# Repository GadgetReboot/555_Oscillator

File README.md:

# 555_Oscillator
555 Oscillator with Duty Cycle and Frequency Control
<br><br><BR><BR>

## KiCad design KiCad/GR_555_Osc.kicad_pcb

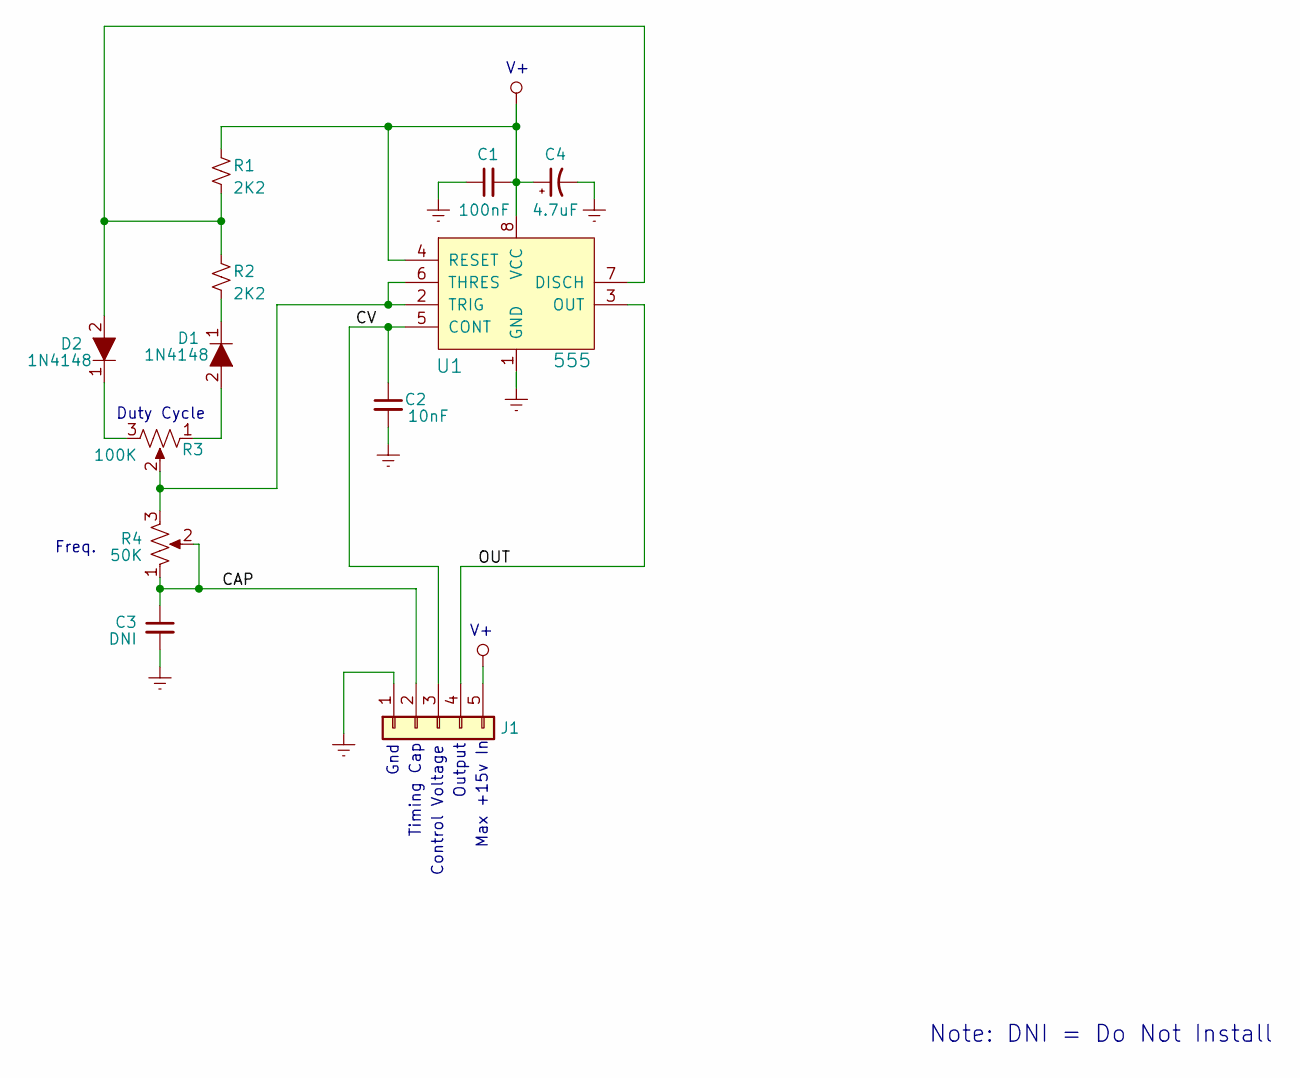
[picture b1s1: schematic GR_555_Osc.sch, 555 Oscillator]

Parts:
C1: 100nF; C_Disc_D3.8mm_W2.6mm_P2.50mm
C2: 10nF; C_Disc_D3.8mm_W2.6mm_P2.50mm
C3: DNI; C_Disc_D3.8mm_W2.6mm_P2.50mm
C4: 4.7uF; CP_Radial_D5.0mm_P2.50mm
D1, D2: 1N4148; Diode_DO-35_P10mm; MPN 1N4148; Digi-Key_PN 1N4148FS-ND
J1: Conn_01x05; PinHeader_1x05_P2.54mm_Vertical
R1, R2: 2K2; R_Axial_DIN0207_L6.3mm_D2.5mm_P10.16mm_Horizontal
R3: 100K; Potentiometer_Bourns_PTV09A-1_Single_Vertical
R4: 50K; Potentiometer_Bourns_PTV09A-1_Single_Vertical
U1: 555; DIP-8_W7.62mm; MPN NE555P; Digi-Key_PN 296-1411-5-ND

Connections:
/CAP: C3.1, J1.2, R4.1, R4.2
/CV: C2.1, J1.3, U1.5 (CONT)
/OUT: J1.4, U1.3 (OUT)
GNDREF: C1.1, C2.2, C3.2, C4.2, J1.1, U1.1 (GND)
unnamed: D1.1, R2.1
unnamed: D1.2, R3.1
unnamed: D2.1, R3.3
unnamed: D2.2, R1.1, R2.2, U1.7 (DISCH)
unnamed: R3.2, R4.3, U1.2 (TRIG), U1.6 (THRES)
VCC: C1.2, C4.1, J1.5, R1.2, U1.4 (RESET), U1.8 (VCC)

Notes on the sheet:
Max +15v In
Gnd
Output
Control Voltage
Timing Cap
Duty Cycle
Freq.
Note: DNI = Do Not Install

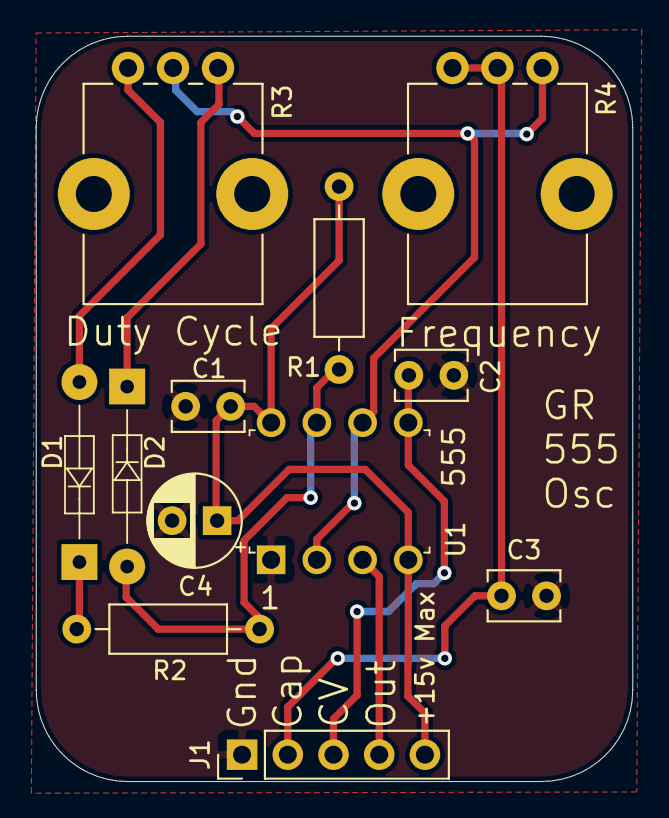
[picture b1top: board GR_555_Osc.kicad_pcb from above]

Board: 2 copper layers, 33.1 x 41.4 mm, 12 parts (0 on the bottom side), 10 nets.
